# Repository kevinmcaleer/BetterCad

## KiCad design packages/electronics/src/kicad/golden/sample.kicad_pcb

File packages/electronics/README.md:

# @bettercad/electronics

The electronics design model (epic #606): components, schematic sheets, the board, and the logic that ties them
together. Framework-free: no React, no three.js, no DOM.

- `model.ts`: the types saved in a `.bcad` file under `electronics`.
- `geom.ts`: 2D helpers. Millimetres, x to the right, y up.
- `nets.ts`: works out the nets from wires, labels, junctions and power symbols.
- `sync.ts`: the change list that keeps the board in step with the schematic.

See `docs/electronics.md`.

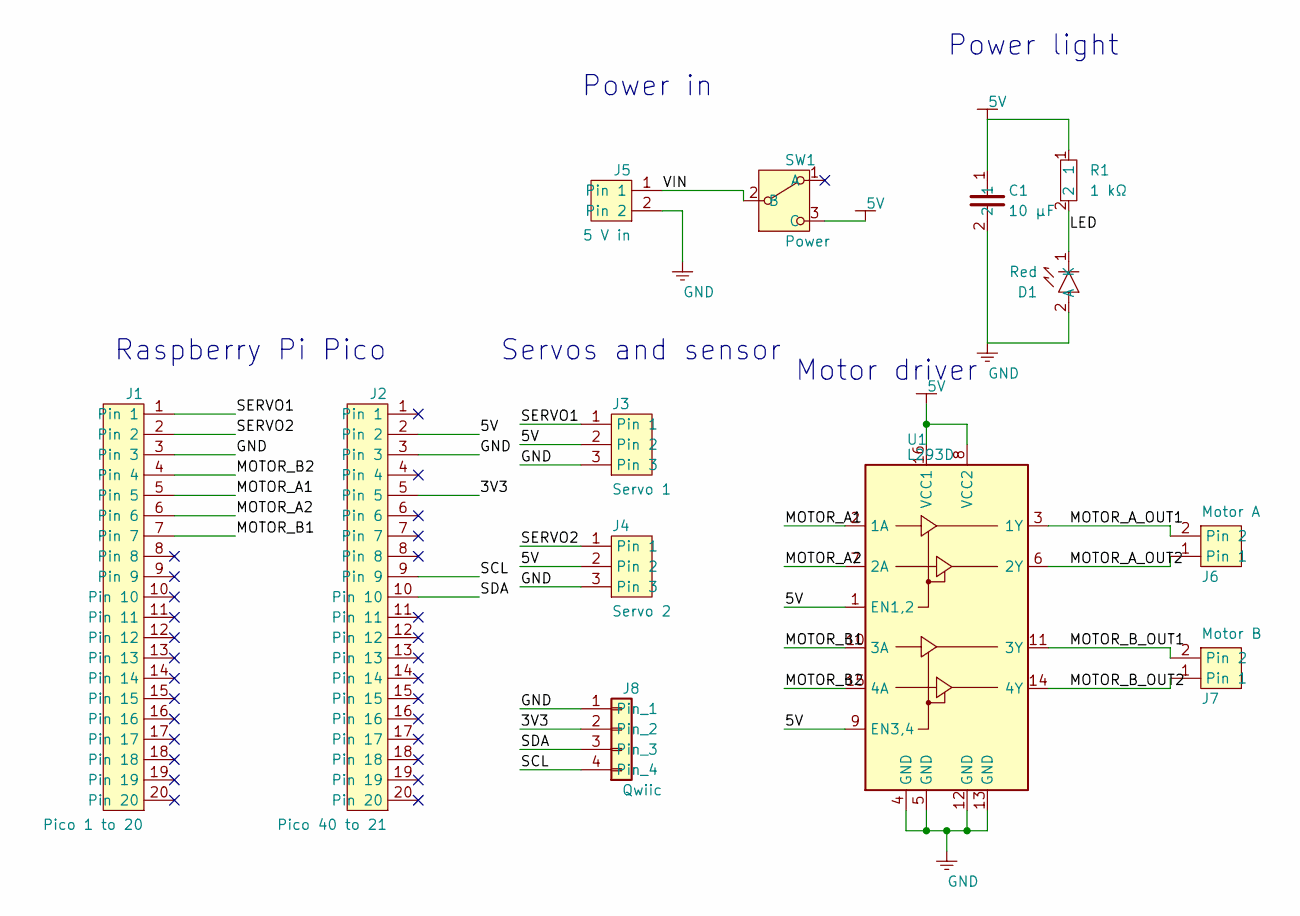
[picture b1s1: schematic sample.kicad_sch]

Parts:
C1: 10 µF; 0805_2012_metric; MPN CL21A106KAYNNNE; LCSC C15850
D1: Red; 0805_2012_metric; MPN NCD0805R1; LCSC C84256
J1: Pico 1 to 20; Pin_header_1_20_2.54_mm; MPN KH-2.54FH-1X20P-H8.5; LCSC C2905423
J2: Pico 40 to 21; Pin_header_1_20_2.54_mm; MPN KH-2.54FH-1X20P-H8.5; LCSC C2905423
J3: Servo 1; Pin_header_1_3_2.54_mm; MPN PZ254V-11-03P; LCSC C2937625
J4: Servo 2; Pin_header_1_3_2.54_mm; MPN PZ254V-11-03P; LCSC C2937625
J5: 5 V in; Pin_header_1_2_2.54_mm; MPN PZ254V-11-02P; LCSC C492401
J6: Motor A; Pin_header_1_2_2.54_mm; MPN PZ254V-11-02P; LCSC C492401
J7: Motor B; Pin_header_1_2_2.54_mm; MPN PZ254V-11-02P; LCSC C492401
J8: Qwiic; JST_SH_SM04B-SRSS-TB_1x04-1MP_P1.00mm_Horizontal; MPN SM04B-SRSS-TB(LF)(SN); LCSC C160404
R1: 1 kΩ; 0805_2012_metric; MPN 0805W8F1001T5E; LCSC C17513
SW1: Power; SW_SPDT_PCM12; MPN PCM12SMTR; LCSC C221841
U1: L293D; DIP-16_W7.62mm; MPN L293DNE; LCSC C701118

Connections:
3V3: J2.5 (Pin 5), J8.2
5V: C1.1, J2.2 (Pin 2), J3.2 (Pin 2), J4.2 (Pin 2), R1.1, SW1.3 (C), U1.1 (EN1,2), U1.8 (VCC2), U1.9 (EN3,4), U1.16 (VCC1)
GND: C1.2, D1.2 (A), J1.3 (Pin 3), J2.3 (Pin 3), J3.3 (Pin 3), J4.3 (Pin 3), J5.2 (Pin 2), J8.1, U1.4 (GND), U1.5 (GND), U1.12 (GND), U1.13 (GND)
LED: D1.1 (K), R1.2
MOTOR_A1: J1.5 (Pin 5), U1.2 (1A)
MOTOR_A2: J1.6 (Pin 6), U1.7 (2A)
MOTOR_A_OUT1: J6.2 (Pin 2), U1.3 (1Y)
MOTOR_A_OUT2: J6.1 (Pin 1), U1.6 (2Y)
MOTOR_B1: J1.7 (Pin 7), U1.10 (3A)
MOTOR_B2: J1.4 (Pin 4), U1.15 (4A)
MOTOR_B_OUT1: J7.2 (Pin 2), U1.11 (3Y)
MOTOR_B_OUT2: J7.1 (Pin 1), U1.14 (4Y)
SCL: J2.9 (Pin 9), J8.4
SDA: J2.10 (Pin 10), J8.3
SERVO1: J1.1 (Pin 1), J3.1 (Pin 1)
SERVO2: J1.2 (Pin 2), J4.1 (Pin 1)
VIN: J5.1 (Pin 1), SW1.2 (B)

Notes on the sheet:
Raspberry Pi Pico
Servos and sensor
Motor driver
Power in
Power light

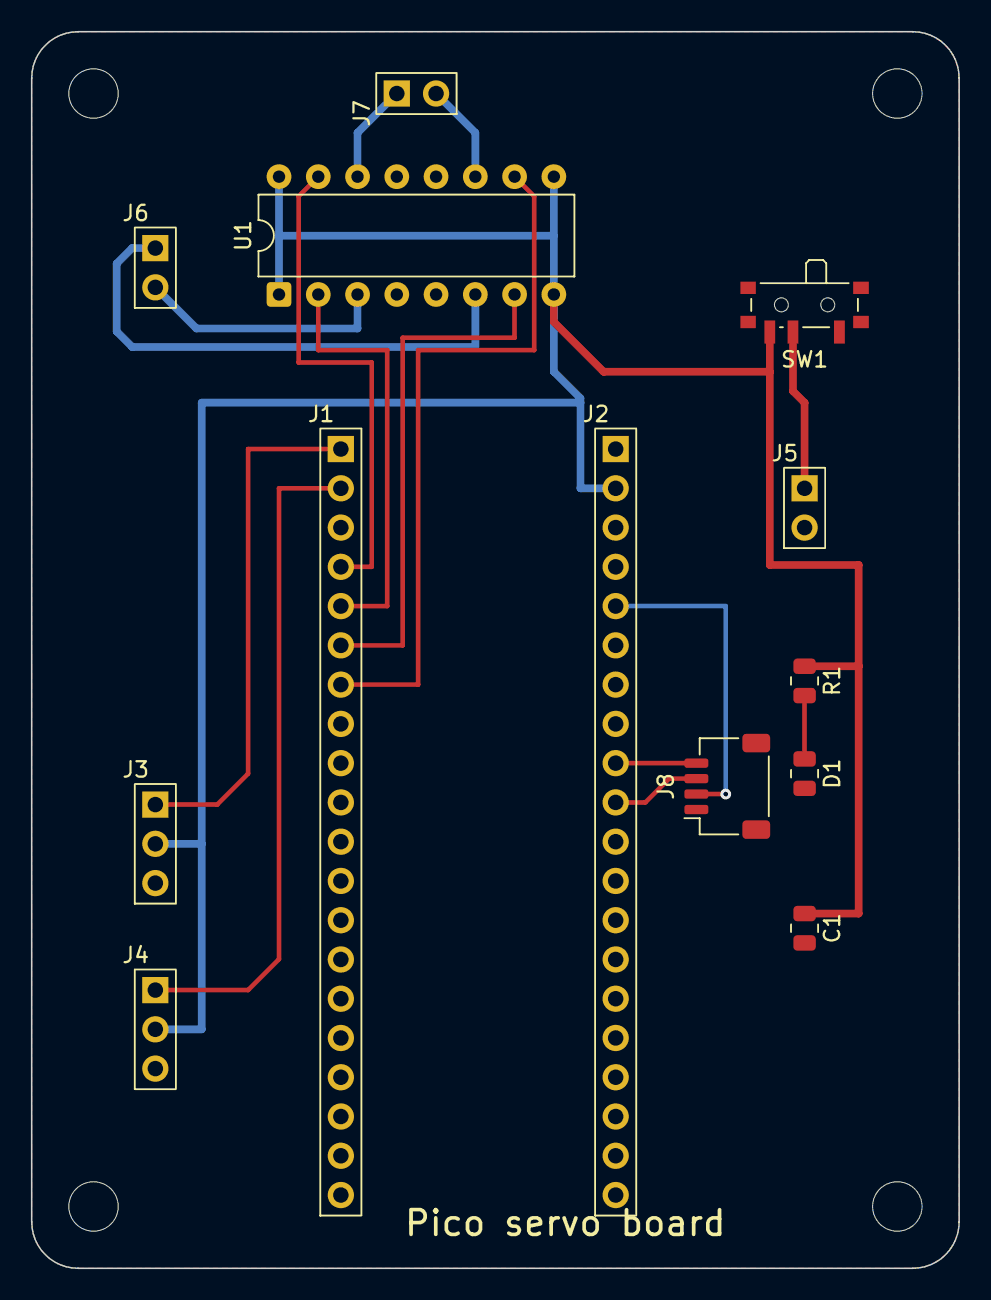
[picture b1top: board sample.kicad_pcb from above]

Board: 2 copper layers, 60.0 x 80.0 mm, 17 parts (0 on the bottom side), 17 nets.

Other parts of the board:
H: Hole; Hole_3.2mm
H#2, H#3, H#4: Hole; Hole_3.2mm

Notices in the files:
parts and their libraries:
Generic connector, single row, 01x04, script generated (kicad-library-utils/schlib/autogen/connector/). From KiCad libraries 9.0.0, CC-BY-SA 4.0 with exception.
Quadruple Half-H Drivers. From KiCad libraries 9.0.0, CC-BY-SA 4.0 with exception.
